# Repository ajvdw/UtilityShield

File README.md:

# UtilityShield
Solar, Power and Water meter shield for Wemos v2 (ESP8266)

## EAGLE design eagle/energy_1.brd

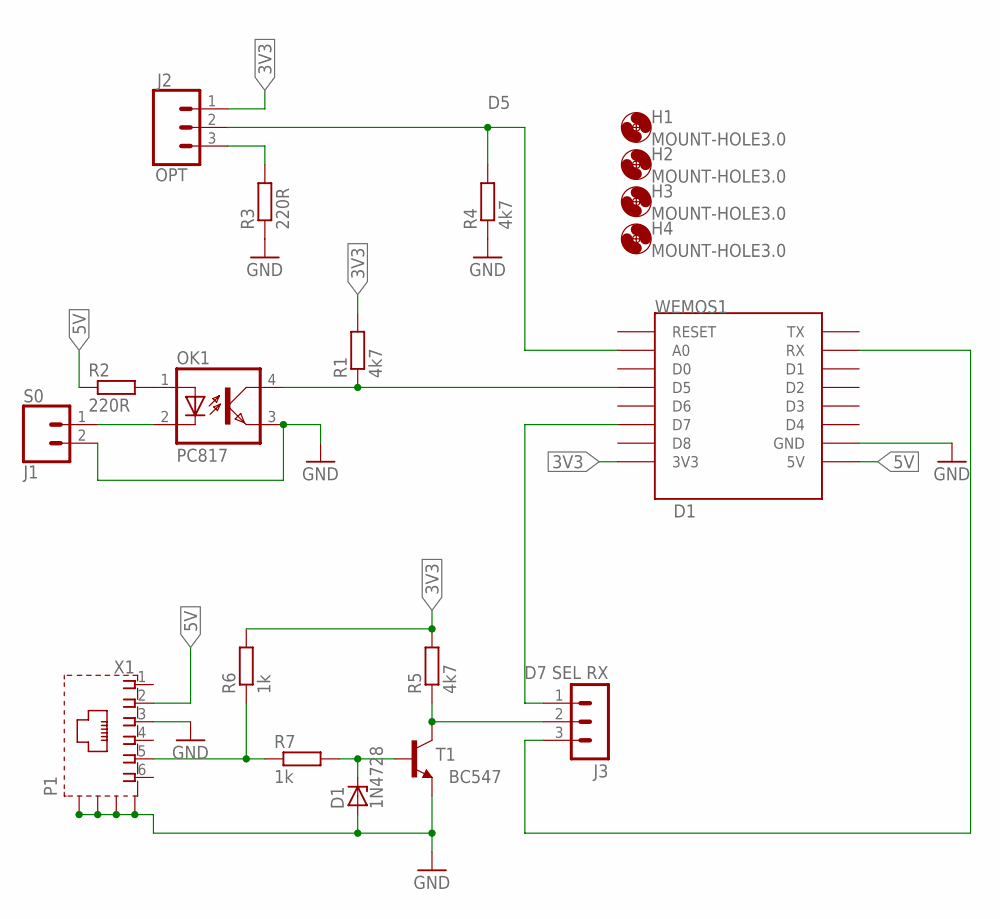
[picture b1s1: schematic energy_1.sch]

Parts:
D1: 1N4728; DO41Z10
H1, H2, H3, H4: MOUNT-HOLE3.0; 3,0
J1: S0; SCREWTERMINAL-3.5MM-2
J2: OPT; SCREWTERMINAL-3.5MM-3
J3: D7 SEL RX; MA03-1
OK1: PC817; DIL04
R1, R4, R5: 4k7; 0207/10
R2, R3: 220R; 0207/10
R6, R7: 1k; 0207/10
T1: BC547; TO92
WEMOS1: D1; WEMOS-D1-MINI
X1: P1; RJ11-SHIELD2

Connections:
3V3: J2.1, R1.2, R5.2, R6.2, WEMOS1.3V3
5V: R2.1, WEMOS1.5V, X1.2
D5: OK1.4 (COL), R1.1, WEMOS1.D5
D7: J3.2, R5.1, T1.3 (C)
GND: D1.A, J1.2, OK1.3 (EMIT), R3.1, R4.1, T1.1 (E), WEMOS1.GND, X1.3, X1.S1 (S), X1.S2 (S), X1.S3 (S), X1.S4 (S)
unnamed: D1.C, R7.2, T1.2 (B)
unnamed: J1.1, OK1.2 (C)
unnamed: J2.3, R3.2
unnamed: R6.1, R7.1, X1.5
unnamed: J3.1, WEMOS1.D7
unnamed: J3.3, WEMOS1.RX
unnamed: OK1.1 (A), R2.2
NPNOUT: J2.2, R4.2, WEMOS1.A0

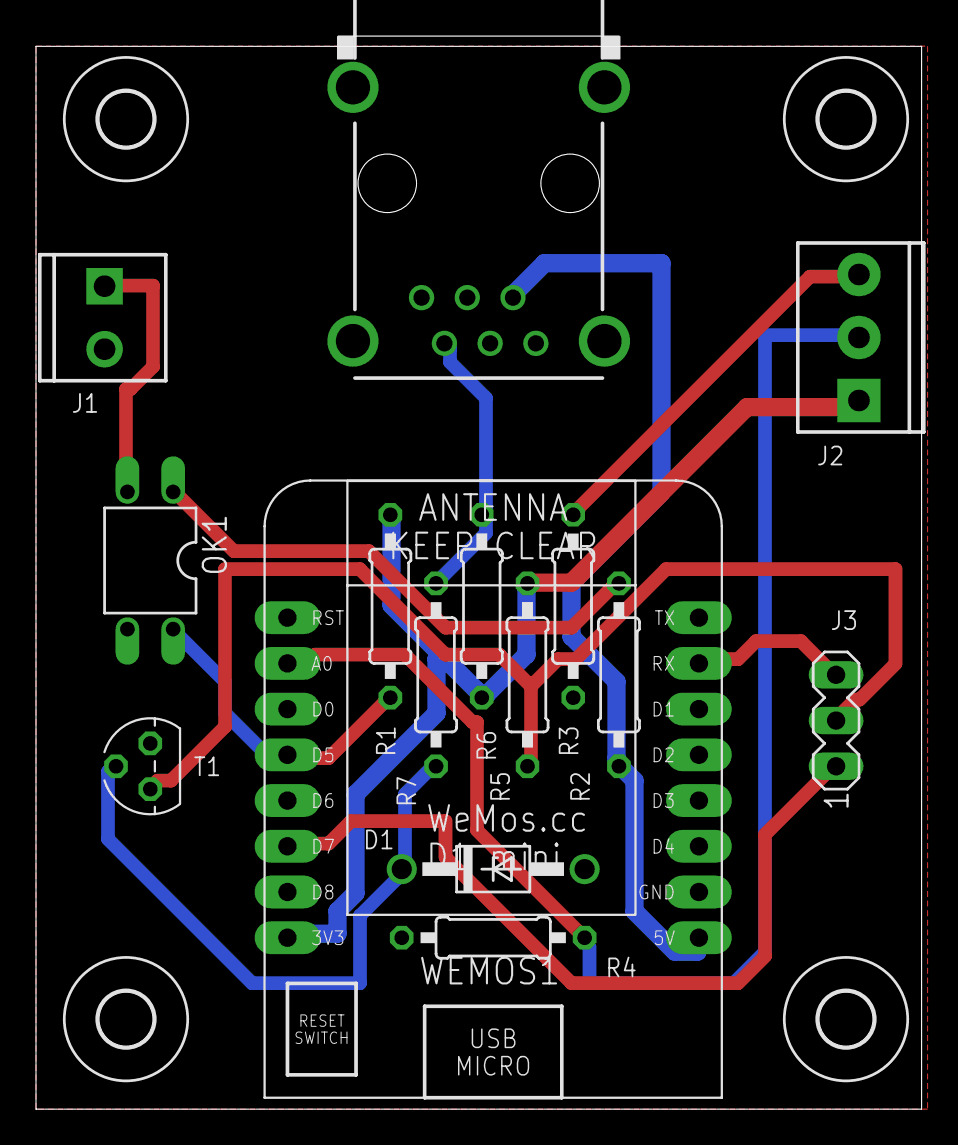
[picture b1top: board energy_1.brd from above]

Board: 2 copper layers, 49.2 x 59.6 mm, 19 parts (0 on the bottom side), 13 nets.

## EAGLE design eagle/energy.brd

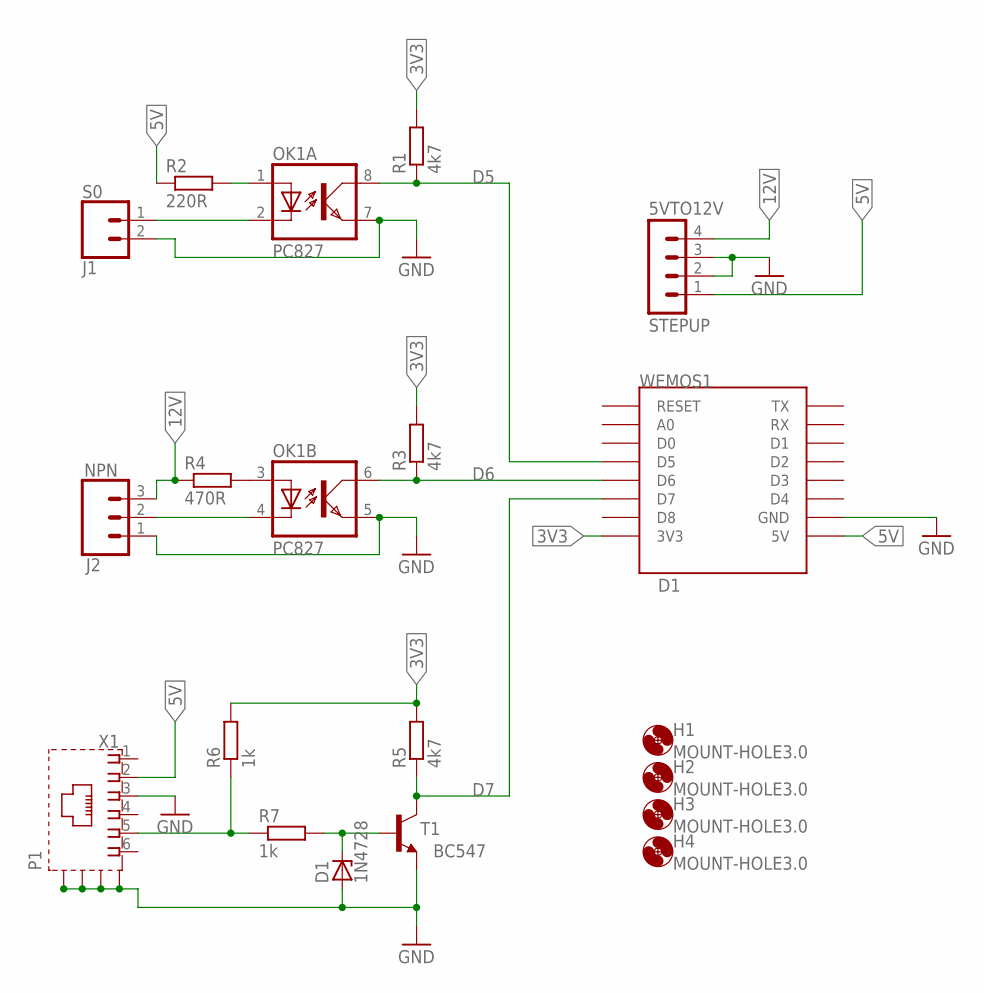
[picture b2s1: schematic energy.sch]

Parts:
5VTO12V: STEPUP; MA04-1
D1: 1N4728; DO41Z10
H1, H2, H3, H4: MOUNT-HOLE3.0; 3,0
J1: S0; SCREWTERMINAL-3.5MM-2
J2: NPN; SCREWTERMINAL-3.5MM-3
OK1: PC827; DIL08
R1, R3, R5: 4k7; 0207/10
R2: 220R; 0207/10
R4: 470R; 0207/10
R6, R7: 1k; 0207/10
T1: BC547; TO92
WEMOS1: D1; WEMOS-D1-MINI
X1: P1; RJ11-SHIELD2

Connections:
3V3: R1.2, R3.2, R5.2, R6.2, WEMOS1.3V3
5V: 5VTO12V.1, R2.1, WEMOS1.5V, X1.2
12V: 5VTO12V.4, J2.3, R4.1
D5: OK1.8 (COL), R1.1, WEMOS1.D5
D6: OK1.6 (COL), R3.1, WEMOS1.D6
D7: R5.1, T1.3 (C), WEMOS1.D7
GND: 5VTO12V.2, 5VTO12V.3, D1.A, J1.2, J2.1, OK1.5 (EMIT), OK1.7 (EMIT), T1.1 (E), WEMOS1.GND, X1.3, X1.S1 (S), X1.S2 (S), X1.S3 (S), X1.S4 (S)
unnamed: D1.C, R7.2, T1.2 (B)
unnamed: J1.1, OK1.2 (C)
unnamed: OK1.3 (A), R4.2
unnamed: R6.1, R7.1, X1.5
unnamed: OK1.1 (A), R2.2
NPNOUT: J2.2, OK1.4 (C)

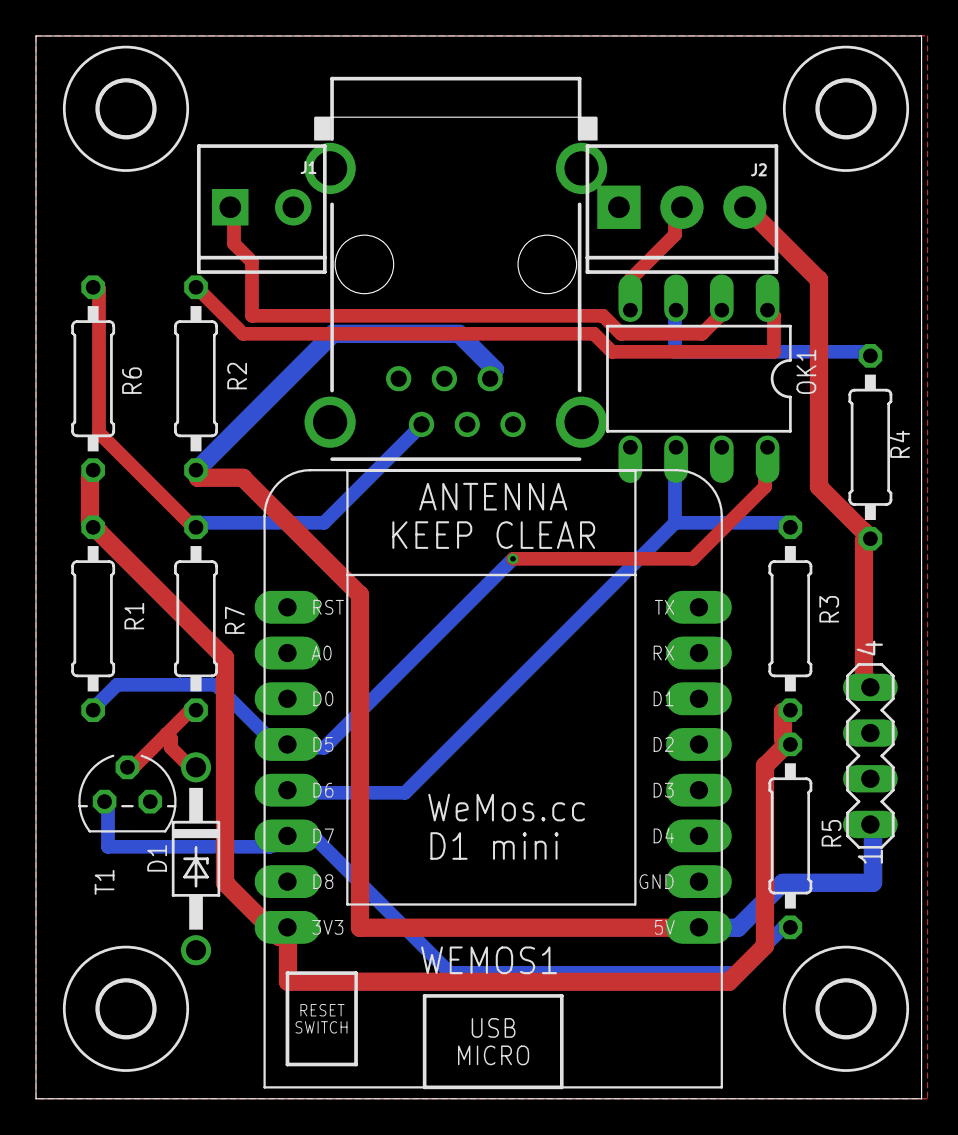
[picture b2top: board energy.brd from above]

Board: 2 copper layers, 49.2 x 59.0 mm, 19 parts (0 on the bottom side), 13 nets.

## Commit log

2017-05-26 Adjusted PCB
2017-05-27 Before moving to WifiManager
2017-05-31 Improved Strength
2017-05-31 Interrupt handlers are now working
2017-06-05 Improve measurement of water flow
2017-12-18 v0.41
2017-12-19 TimeSync improved
2017-12-20 Cleaning up
2017-12-20 Removing Unused stuff
2017-12-30 Added WeatherUnderground
2017-12-30 Changed indentation
2017-12-30 indents
2018-01-01 Some cleanup
2018-01-05 Added DSMR parsing
    Not fully tested yet
2018-01-14 Improved Timesync

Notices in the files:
parts and their libraries:
SparkFun-Connectors: Licensing: Creative Commons ShareAlike 4.0 International - https://creativecommons.org/licenses/by-sa/4.0
